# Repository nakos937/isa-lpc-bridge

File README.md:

# isa-lpc-bridge: a real 16-bit ISA slot on a modern motherboard, through the TPM header

A riser board with one **16-bit ISA slot** that connects to a modern PC through its **TPM header (LPC bus)**.
It is meant for **legacy ISA cards under DOS and DOS-based systems**: sound cards (Sound Blaster, Gravis UltraSound, Orpheus II, ...), I/O and
serial cards, and other I/O-mapped cards with IRQ and DMA.
Like [dISAppointment](https://github.com/rasteri/dISAppointment), but with a microcontroller (RP2354B, firmware in C) in
place of the Fintek F85226 bridge chip, so the whole thing is open and tweakable, and does not rely on a custom, hard to get ASIC.

> **Status.** Revision `PASS_HG25` works. Tested by the author with a **Sound Blaster 16, Gravis UltraSound, GUS PnP,
> Orpheus II and a generic OPL3-SAx card** (all working without problems, **including DMA** through the LDRQ# wire) and an ISA **floppy/COM port card**. Cards in the table below that are not marked
> *tested* are expected to work from datasheets and Linux driver sources. Reports and fixes are welcome.

*3D renders from KiCad. The ISA socket and the power connector have no 3D model in the render and show as pads/outline.*

## Base specs

| | |
|---|---|
| Board | 240.1 x 36.1 mm, 4 layers, 1.6 mm, single sided assembly |
| Slot | one 98-pin 16-bit ISA edge socket (ED98KBGFBK, LCSC C5173323) |
| Host link | 2x9 right-angle header wired 1:1 to the common 17/18-pin "TPM header": LCLK, LFRAME#, LAD0-3, SERIRQ, PCIRST#, GND (**3.3 V logic**) |
| LDRQ# | one extra wire, **not on the TPM header** (see [Getting LDRQ#](#getting-ldrq-needed-for-dma)) |
| Power | from the PSU through a 4-pin floppy (Berg) power connector: +5 V and +12 V. -12 V, -5 V and 3.3 V are made on the board |
| MCU | RP2354B (QFN-80, 2 MB internal flash), 400 MHz default, programmed over SWD (no USB on the board) |
| Provides | ISA I/O cycles, 8-bit and 16-bit DMA (channels 0-3 and 5-7), IRQ 3-7, 9-12, 14, 15 and IOCHCK# through SERIRQ, ISA reset |
| Does not provide | ISA memory cycles, bus mastering, refresh, MEMCS16#/OWS# sensing |
| Host tool | `ISALPC.EXE` (DOS) / `isalpc` (Linux): programs the chipset's LPC decode windows and the bridge, with presets for common cards |

```mermaid
flowchart LR
  PCH["PC chipset (PCH)\nLPC bus"] -- "TPM header: LCLK LFRAME# LAD0-3\nSERIRQ PCIRST# GND" --> J4["J4 on the board"]
  PCH -. "LDRQ# (wire from a test point)" .-> J4
  J4 --> MCU["RP2354B\n3 PIO state machines\n= LPC target"]
  MCU --> ISA["address shift registers\nIRQ input registers\n5 V buffers + level shifters"]
  ISA --> SLOT["16-bit ISA slot\n(sound card)"]
  PSU["PSU floppy connector\n+5 V / +12 V"] --> PWR["fuses, filters,\n3.3 V, -12 V, -5 V"] --> SLOT
```

## Contents
1. [Who this is for and what you need](#who-this-is-for-and-what-you-need)
2. [Compatibility](#compatibility)
3. [Mounting it in a case](#mounting-it-in-a-case)
4. [Wiring](#wiring)
5. [Getting LDRQ#](#getting-ldrq-needed-for-dma)
6. [First power-up checklist](#first-power-up-checklist)
7. [Firmware](#firmware)
8. [Host setup: ISALPC](#host-setup-isalpc)
9. [Motherboard BIOS notes](#motherboard-bios-notes)
10. [Building everything](#building-everything)
11. [Repository layout](#repository-layout)
12. [Quirks and limits](#quirks-and-limits)
13. [Credits and licenses](#credits-and-licenses)

## Who this is for and what you need
- A motherboard with a **TPM header that carries the LPC bus** and a chipset whose LPC bridge can forward I/O ranges (Intel PCH
  generic decode ranges; AMD works with [lpcexp](https://github.com/lss4/lpcexp) but is not covered by our tool).
- Soldering skills: the board is assembled by the fab, but you must **wire LDRQ#** to the motherboard (a fine wire to a test
  point or resistor pad) if you want DMA.
- An SWD probe (CMSIS-DAP: Raspberry Pi Debug Probe, a Pico running picoprobe, ...) and OpenOCD to load the firmware.
- A PSU with a spare floppy power plug (the one with 4 wires: red +5 V, black, black, yellow +12 V).
- A DOS boot environment on the host (MS-DOS/FreeDOS/Win9x on a legacy/CSM boot).
- A scope or logic analyser is strongly recommended for bring-up. Nothing has been measured on silicon yet.

## Compatibility

### Motherboards / chipsets
| Host | I/O + IRQ | DMA | Notes |
|---|---|---|---|
| **ASRock Fatal1ty X99M Killer** (Intel X99 / C610) | works | **works** (with the LDRQ# wire) | BIOS analysed in [docs/bios-x99m-killer-p4.01.md](docs/bios-x99m-killer-p4.01.md); 17-pin TPMS1 header |
| Other Intel chipsets **before the 100 series** (6/7/8/9 series, X79/X99/C600) | expected | expected, needs LDRQ# wire | LPC DMA exists on these. Header pinouts differ per board: check with a meter |
| Intel **100 series and newer** (Skylake and later) | expected (GEN decode ranges exist) | **no**: Intel removed LDRQ# from the 100 series on | FM synthesis, MIDI and PIO sound work; digitised audio in DOS games needs DMA and will not. See the [lpcexp readme](https://github.com/lss4/lpcexp) |
| AMD (AM4 and similar) | use lpcexp (AMD code), not `isalpc` | AM4: unknown to us; **AM5/SP5: no LDRQ#** | not covered |

### Sound cards (*tested* = tried by the author; otherwise expected from datasheets and Linux driver sources)
The `ISALPC` presets in parentheses set up the chipset and the bridge for the card.

| Card | Status | Notes |
|---|---|---|
| Sound Blaster 1.x/2.0/Pro, **Sound Blaster 16** (`sb`, `sb16`) | **tested**, works (SB16) | byte I/O only. 8-bit DMA 1, 16-bit DMA 5. IRQ 5/7. MPU-401 at 330 |
| AdLib, OPL2/OPL3 (`adlib`) | expected (the OPL3 on the tested cards works) | ports 388-38B, no IRQ or DMA |
| **Gravis UltraSound** classic (`gus`, `gusmax`) | **tested**, works | base 240; word access on base+0x104 is handled |
| **GUS PnP / AMD InterWave** (`guspnp`) | **tested**, works | needs the ISA PnP ports (279, A79, read port) forwarded: `@pnp` is included |
| **Orpheus II** (`orpheus2`) | **tested**, works | CS4237B + InterWave + OPL3 + PCMIDI; needs all four LPC windows. WSS at 534 collides with the chipset GPIO block on some boards (the X99M): `ISALPC` moves that block, **DOS only** (works on the X99M: tested with the Orpheus II) |
| **AWE32/AWE64** (`awe32`) | expected | the EMU8000 uses 16-bit I/O (ports 620/A20/E20): supported. Needs five 256-port blocks, which is more than the chipset has windows for unless you free the Super I/O and COM decodes |
| **Yamaha OPL3-SAx** (`opl3sa`) | **tested**, works (generic card) | |
| ESS AudioDrive, Crystal CS423x, WSS (`ess`, `cs423x`, `wss`) | expected | WSS base 530 is inside the GPIO block on X99M-like boards (see above) |
| MPU-401 interfaces, Roland SCC-1/LAPC-I (`mpu401`) | expected | the board makes -12 V and -5 V |
| Pro Audio Spectrum 16 | **impossible** | its registers span 19 port blocks, the chipset has four decode windows |
| Turtle Beach MultiSound / Pinnacle / Fiji, any card with an on-board memory window | **not supported** | needs ISA *memory* cycles. UEFI hosts occupy that memory space anyway |
| ADI/Echo PSS | possible | 16-bit reads need an entry in `word_rd` (a commented line is in `fw/src/main.c`) |
| Floppy, COM, LPT, IDE, NE2000, SCSI ISA cards (`fdc`, `com1`, `lpt1`, `ide1`, `ne2000`, ...) | floppy + COM card **tested**, works; the other presets exist but are not the project's goal | disable the onboard ports in the BIOS first, or both answer |

Cards the author has no access to are marked *expected* and have not been tried: more test reports are welcome.

Not intended: ISA VGA cards, bus-mastering cards, cards that need ISA memory.

## Mounting it in a case
- The board is **240 mm long and 36 mm wide**. It is made for a case with **two free PCI/expansion slot positions** next to
  each other (a microATX or ATX board with the lower slots empty); measure your case before ordering.
- There are **no mounting holes**. Hold it with **thick double-sided foam tape or plastic spacers/standoffs under the board**.
  Without support the board flexes when you insert a card: the socket datasheet gives up to 0.4 kgf per contact pair, which is up to roughly 20 kgf for a full 98-pin card, so use a
  firm, even base and push the card in while holding the board down.
- The ISA socket is a straight edge socket: the **card stands up from the board** (its bottom edge sits about 8 mm above
  the PCB). Check clearance to the neighbouring PCIe cards, the case ribs and the card's own bracket. The card bracket
  **may not line up with a case slot** (it depends on your case): expect to leave it unscrewed or use a bracket-less mount.
- Cables leave from the long edge at the right end: the power plug (J1), the SWD header (J2) and the 2x9 TPM-style header
  (J4) are right-angle parts. The tall parts are the three headers and the power connector.
- Keep the LPC wiring **short** (10 cm or less) and use the ground pins of J4.

## Wiring

### Power connector J1 (4-pin floppy/Berg, right angle)
| Pin | Signal |
|---|---|
| 1 | +5 V (red wire) |
| 2, 3 | GND |
| 4 | +12 V (yellow wire) |

Fuses: 2.6 A hold on +5 V, 1.5 A hold on +12 V (resettable). Surge clamps on both rails.

### Host header J4 (2x9, 2.54 mm, right angle)
Wired 1:1 to the ASRock-style TPM header. Pin numbers as on the standard 20-1-pin TPM layout (odd pins in one row, even in
the other; **pin 13 is the key position and missing on the motherboard header**). Always verify against *your* board.

| J4 pin | Signal | Pin | Signal |
|---|---|---|---|
| 1 | LCLK (PCICLK) | 2 | GND |
| 3 | LFRAME# | 4 | not connected |
| 5 | PCIRST# | 6 | not connected |
| 7 | LAD3 | 8 | LAD2 |
| 9 | not connected (+3V on the host) | 10 | LAD1 |
| 11 | LAD0 | 12 | GND |
| **13** | **LDRQ# (100 ohm in series, 4.7 k pull-up to 3.3 V on the board)** | 14 | not connected |
| 15 | not connected (+3VSB on the host) | 16 | SERIRQ |
| 17 | GND | 18 | GND |

The host's +3V, +3VSB, SMBus and S_PWRDWN# pins are **not** connected on purpose.

### SWD header J2 (1x4)
`SWCLK, GND, SWDIO, RUN` (pin 1 at the SWCLK end, marked on the silkscreen).

### Test points
`TP1` +5V_SLOT, `TP2` +12V_SLOT, `TP3` +3V3, `TP4` -12V, `TP5` -5V, `TP6` GND, `TP7` ISA_RUN, `TP8` LCLK, `TP9` BCLK (divided oscillator).

## Getting LDRQ# (needed for DMA)
DMA on the LPC bus is requested by a separate signal, **LDRQ#**. The TPM header does not carry it. You have to take it
from the motherboard yourself. Without it everything else works (I/O cycles, IRQs, FM/OPL music), but anything that needs
DMA (digitised sound in DOS games, SB/GUS sample playback) will not.

1. **Find the signal.** Use the board's boardview. The chipset has an LDRQ0# pin (and some also LDRQ1#). On most boards it runs to the Super I/O chip
   (the one that does COM/LPT/PS-2) and often to a test pad, a series resistor, a 0 ohm link or a via on the way. Look at
   the board's schematic or boardview if you have one, or probe the Super I/O's LDRQ# pin. The signal idles **high at
   3.3 V** and pulses low during a DMA request. It must never be tied to 5 V.
2. **Solder a thin wire** (30 AWG wire-wrap wire is fine) to that point.
3. **Connect the other end to the adapter in one of two ways:**
   - **Directly:** a Dupont jumper wire, or the wire itself, to **J4 pin 13** (the pin that is missing on the motherboard's
     TPM header, so the TPM-style cable can not carry it).
   - **Through the TPM header cable:** if you make or modify a ribbon between the motherboard's TPM header and J4, add the
     wire to the position of pin 13 on the J4 end. Keep the stub short.
4. Keep the wire short, run it next to a ground wire (J4 pins 12/17/18) and away from the clock.
5. **Disable the Super I/O's own LPC DMA users** (floppy, parallel port in ECP mode) in the BIOS, so the Super I/O does not
   drive the same LDRQ# line at the same time.
6. Some chipsets multiplex LDRQ1# with a GPIO. If you picked that pin, `ISALPC ldrq1` switches the pad to LDRQ1#. On the
   author's ASRock X99M Killer (BIOS P4.01) the LDRQ1# pad is already set to its LDRQ function (found by static analysis of the BIOS image).

> **The test point is board specific.** Open your board's **boardview** (or schematic) and look up the LDRQ# / LDRQ0# net
> between the chipset and the Super I/O or the LPC pads. The author's X99M Killer works this way: with the wire in place,
> DMA (digitised audio on the SB16, GUS and Orpheus II) works.

## First power-up checklist
1. Before inserting anything, check **J1 polarity** with a meter: red wire to TP1 (+5 V), yellow to TP2 (+12 V).
2. **Never run the PC with J4 connected and J1 unplugged.** The LPC pins of the MCU are not 5 V tolerant and the host's 3.3 V
   would back-feed an unpowered chip.
3. Plug the PSU connector with the PSU off. Power up *without* the ISA card and *without* J4. Check the rails on the test
   points: +5 V, +12 V, **+3.3 V**, **-12 V (about -12.1 V)** and **-5 V**.
4. Load the firmware over SWD (see below) and check `RESETDRV`/`ISA_RUN` behaviour with a scope.
5. Scope **LCLK** at the MCU pin before connecting J4; the LPC pins are driven by the PIO state machines directly.
6. Connect J4 with the PC off, then power both. Run `ISALPC` and read the status.
7. Only then add a card. Scope the DRQ and IOCHRDY lines at the MCU: if they exceed about 5.4 V with a real card, add a
   series resistor or clamp.
8. Support the board before inserting the card (see [Mounting](#mounting-it-in-a-case)).

## Firmware
Source in [`fw/`](fw/) (pico-sdk 2.1 or newer, `arm-none-eabi-gcc`, cmake, ninja). Pre-built images of build 22:
[`fw/prebuilt/`](fw/prebuilt/) (`isa_lpc_flash_build22.elf`, `isa_lpc_ram_build22.elf`).

- **Architecture:** three PIO blocks implement the LPC target (front end, reply script player, LDRQ#/SERIRQ engines);
  core 1 claims LPC cycles within the 3-clock SYNC deadline; core 0 runs the ISA bus (address through the shift
  registers, strobes, IOCHRDY waits, DMA). Details in [fw/README.md](fw/README.md) and [docs/firmware-review.md](docs/firmware-review.md).
- **Flash:** `fw/tools/flash.sh` (OpenOCD + CMSIS-DAP probe on J2). There is **no USB/BOOTSEL** on the board.
- **No flash needed for development:** `fw/tools/ram.sh` loads the RAM image over SWD; tuning values live in a RAM block
  at `0x2007C000` and can be changed live with OpenOCD (`fw/tools/isa.tcl`).
- **Config port:** the bridge answers on I/O ports **4E/4F** (like the Fintek chip); `ISALPC` uses it. Index 'I','S','A' unlocks
  it. It can be turned off with a flag.
- **Saved config:** `ISALPC ... SAVE` keeps the bridge settings (port filter, IRQ list, timing) in the MCU flash, so the bridge
  answers correctly right after power-up. `ISALPC FORGET` erases them. A save pauses the bridge for up to 1.3 s. Settings
  that could lock the host out are never restored from flash.
- **Tests without hardware:** `python3 fw/sim/test_lpc.py`, `python3 fw/sim/test_aux.py` (cycle simulator of the PIO programs),
  `cc -Ifw/src -o /tmp/t fw/test/io16_test.c && /tmp/t`, same for `cfgport_test.c`.

## Host setup: ISALPC
The chipset forwards only the I/O ranges it was told to, and the bridge claims only the ports of the card you use.
`ISALPC` (DOS, `host/ISALPC.EXE`) or `isalpc` (Linux, as root) does both. **Run it after every boot** (the chipset
windows are reset by the BIOS; the bridge settings live in RAM unless you `SAVE` them): put it in `AUTOEXEC.BAT` before the sound drivers.

```
ISALPC                      show decode windows, SERIRQ, PCI IRQs and the bridge state (writes nothing)
ISALPC SB16                 Sound Blaster 16 at 220, MPU at 330, OPL at 388, game port
ISALPC SB16 FORCE DRY       print what it would do, change nothing
ISALPC GUS=240              Gravis UltraSound at base 240
ISALPC ORPHEUS2 FORCE       Orpheus II: replaces BIOS windows as needed
ISALPC AWE32 FORCE NOPIRQ   AWE32, also turns PCI interrupt routing off for the IRQs the bridge serves
ISALPC LIST                 all presets
```
Options: `SAVE` stores the bridge settings in its flash (`FORGET` erases them), `FORCE` replaces decode windows the BIOS set (as few as needed, highest window first, and it says which),
`DRY` changes nothing, `DMA` resets the DMA controllers (default on DOS), `LDRQ1` switches the GPIO pad to LDRQ1#,
`NOPIRQ` stops routing PCI interrupts to the IRQs the bridge serves, `IRQ=5,7` sets the served IRQs exactly, `GPIO=680` chooses where the chipset GPIO block moves
when a card needs ports inside it (**DOS only**: ACPI operating systems expect the old address).

Limits you will hit: four decode windows of up to 256 ports each, one 256-port block per window; port 279 (ISA PnP address)
is read-only through the LPT decode, so PnP cards need a window. The tool refuses ports inside the chipset's own register
blocks. The DOS part needs Open Watcom to build.

Linux: `cc -O2 -o isalpc host/isalpc.c`, run as root. DOS: `make -C host ISALPC.EXE` with Open Watcom, or use the prebuilt EXE.

## Motherboard BIOS notes
- **Disable onboard COM, LPT, floppy and anything else on the LPC bus you do not need.** They compete for the same ports
  and DMA channels and some use LPC windows the card needs. Keep CSM/legacy boot and legacy USB (for a DOS keyboard).
- No setup option reserves an IRQ for ISA cards: a PCI device can land on the card's IRQ. `ISALPC` lists the IRQs PCI uses
  and `NOPIRQ` can take them away from PCI.
- Serial IRQ must be in **continuous** mode. `ISALPC` sets it; the bridge does not work in quiet mode.
- **ASRock X99M Killer 3.1 BIOS P4.01**: analysed in [docs/bios-x99m-killer-p4.01.md](docs/bios-x99m-killer-p4.01.md): three of the four
  generic decode windows are used, the chipset GPIO block sits at 500-57F (collides with WSS/Orpheus at 530/534), serial IRQ
  starts in quiet mode. An optional patcher ([tools/bios/patch_x99m.py](tools/bios/patch_x99m.py)) frees the unused windows
  from power-on (7 bytes). It checks the sha256 of the original image and edits only what it recognises. Flash modified firmware only if you have an SPI programmer
  and a backup. `ISALPC` does the same at run time, so the patch is optional.

## Building everything
| What | How |
|---|---|
| Firmware | `export PICO_SDK_PATH=...; fw/tools/build.sh` (flash image) or `fw/tools/build.sh ram` |
| DOS tool | Open Watcom 2: `make -C host ISALPC.EXE` (16-bit small model) |
| Linux tool | `cc -O2 -o isalpc host/isalpc.c` |
| Tool self-test | `make -C host test` (fake chipset + the firmware's config-port code) |
| Netlist | `python3 sch/build.py` (SKiDL, KiCad 10 libraries), `python3 tools/netcheck.py` |
| Board | open `pcb/PASS_HG25.kicad_pcb` in **KiCad 10**; custom footprints in `lib/isa_bridge.pretty` (add to your footprint table) |
| Fab files | `fab/PASS_HG25_gerbers.zip`, `fab/bom.csv`, `fab/cpl.csv` (JLCPCB format, LCSC numbers in the BOM) |
| Datasheets | `docs/datasheets/` (index in its README) |
| Independent clearance audit | `tools/review/via_copper_audit.py` (KiCad Python) |

## Repository layout
```
pcb/       KiCad 10 board (PASS_HG25), project and design rules (JLCPCB multilayer minimums)
fab/       gerbers, BOM, placement file, LCSC part map
sch/       build.py: the whole netlist as SKiDL code (no .kicad_sch files)
lib/       custom footprints and symbols, datasheet pin tables
fw/        RP2354B firmware, PIO programs, simulator, tests, prebuilt images
host/      ISALPC (DOS and Linux) and its self-test
tools/     netlist checker, symbol generator, BIOS analysis scripts, clearance audit
docs/      pin map, BIOS analysis, card I/O survey, reviews, order notes
images/    renders
```

## Quirks and limits
- Run `ISALPC` at every boot: the BIOS resets the chipset's decode windows each time. The bridge's own settings can be kept in its flash with `ISALPC ... SAVE`, otherwise they are lost at power-off.
- 5 V logic on the ISA side through buffers; the MCU side is 3.3 V. `IOCS16#` is sensed after each address change.
- There is no USB, no BOOTSEL button: a failed flash needs an SWD probe. The RAM image avoids flashing altogether.
- The hand-wired LDRQ# makes this a **hobby/experimenter board**, not a plug-and-play product.
- 400 MHz at 1.30 V is the default (allowed window 340-500 MHz). Put a heatsink the size of the MCU (10 x 10 mm) on it with thermal tape.
- ISA PnP cards need a decode window for the PnP ports; combined with a four-window limit this restricts what fits
  (AWE32 + PnP does not).

## Credits and licenses
- Idea and the DOS tool's concept: **rasteri's [dISAppointment](https://github.com/rasteri/dISAppointment)** (CC BY-SA 4.0): ISA socket
  footprint, pull-up network, `sapphisa`; **[lpcexp](https://github.com/lss4/lpcexp)** (CC BY-SA 4.0): chipset
  register programming; both share the DMA reset register list with `ISALPC`. The MCU power circuit follows Raspberry Pi's RP2350 minimal design (MIT).
- **Board, firmware, host tool, scripts, docs: GPL-2.0-or-later.** The ISA socket footprint and the pull-up
  values come from dISAppointment and stay CC BY-SA 4.0.
  See [LICENSE.md](LICENSE.md) and [LICENSES/](LICENSES/).
- No warranty. Plugging a PSU into a board you assembled yourself, and wiring to a motherboard with a soldering iron,
  can destroy both. You do it at your own risk.

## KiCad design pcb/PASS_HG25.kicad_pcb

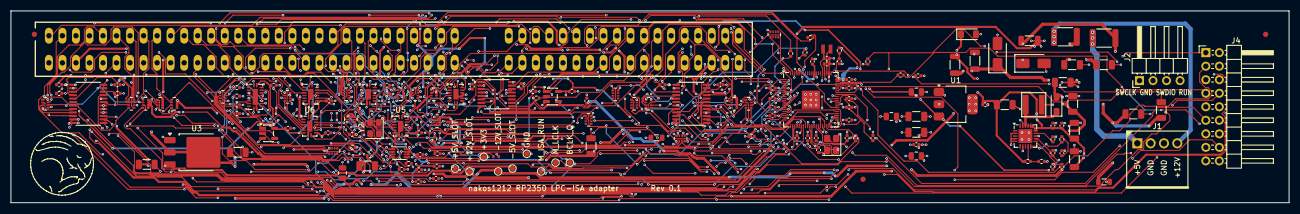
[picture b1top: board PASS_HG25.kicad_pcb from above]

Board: 4 copper layers, 240.0 x 36.0 mm, 166 parts (0 on the bottom side), 189 nets.

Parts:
C1: 47u/10V; C_1206_3216Metric
C2, C4, C21, C22, C26, C28, C67: 10u/25V; C_1206_3216Metric
C3, C7, C14: 22u/25V; C_1206_3216Metric
C5, C16, C17: 22u/10V; C_1206_3216Metric
C6, C8, C10, C11, C12, C13, C15, C23, C33, C34, C35, C36, C37, C38, C39, C40, C41, C42, C43, C44, C45, C50, C51, C52, C53, C54, C55, C56, C57, C58, C59, C60, C61, C62, C63, C64, C65, C66, C68, C69: 100n; C_0402_1005Metric
C9, C18, C46, C47: 10u/10V; C_0805_2012Metric
C19, C20: 1u/16V; C_0402_1005Metric
C24: 1u/25V; C_0402_1005Metric
C25: 10u/50V; C_1206_3216Metric
C27: 22n; C_0402_1005Metric
C29, C30, C31, C32: 4.7u/10V; C_0402_1005Metric
C48, C49: 15p; C_0402_1005Metric
D1: SMAJ5.0A; D_SMA
D2: SMAJ13A; D_SMA
D3: SMF12A; D_SOD-123FL_1.1x1.5
D4: DFLS240; D_SOD-123FL_1.1x1.5
F1: 1812L260/12MR; Fuse_1812_4532Metric
F2: 1812L150/24MR; Fuse_1812_4532Metric
FB1, FB2, FB4: BLM31KN601SN1L; L_1206_3216Metric
FB3, FB5: BLM21PG221SN1D; L_0805_2012Metric
FID1, FID2, FID3: Fiducial
G1: rabbit
J1: Berg_Floppy_Power_4P; Berg_171826-4_1x04_P2.50mm
J2: PROG_SWD; PinHeader_1x04_P2.54mm_Horizontal
J3: ISA_16bit_Socket; ISA
J4: TPMS1_LPC; PinHeader_2x09_P2.54mm_Horizontal
L1: 15u NR4030S150MT; L_NR4030
L2: 3.3u AOTA-B201610S3R3-101-T; L_Abracon_AOTA-B201610S3R3-101-T
R1: 200k; R_0402_1005Metric
R2: 47k; R_0402_1005Metric
R3: 1M; R_0402_1005Metric
R4: 62k; R_0402_1005Metric
R5: 15k; R_0402_1005Metric
R6, R21, R22, R23, R24, R25, R26: 33; R_0402_1005Metric
R7, R18: 1k; R_0402_1005Metric
R8, R14, R15, R16, R17, R27: 10k; R_0402_1005Metric
R9, R10, R11, R12, R13, R19: 4.7k; R_0402_1005Metric
R20: 100; R_0402_1005Metric
RN1, RN2: 1k; R_Array_Convex_4x0402
RN3, RN4, RN5, RN16, RN17: 4.7k; R_Array_Convex_4x0402
RN6, RN7, RN8, RN9, RN10, RN11, RN12, RN13, RN14, RN15: 8.2k; R_Array_Convex_4x0402
RN18: 33; R_Array_Convex_4x0402
RN19, RN20, RN21, RN22: 68; R_Array_Convex_4x0402
TP1: +5V_SLOT; TestPoint_Pad_D1.0mm
TP2: +12V_SLOT; TestPoint_Pad_D1.0mm
TP3: +3V3; TestPoint_Pad_D1.0mm
TP4: -12V_SLOT; TestPoint_Pad_D1.0mm
TP5: -5V_SLOT; TestPoint_Pad_D1.0mm
TP6: GND; TestPoint_Pad_D1.0mm
TP7: M_ISA_RUN; TestPoint_Pad_D1.0mm
TP8: M_LCLK; TestPoint_Pad_D1.0mm
TP9: BCLK_Q; TestPoint_Pad_D1.0mm
U1: BL9110-330BPFB; SOT-223-3_TabPin2
U2: ADP5071ACPZ; LFCSP-20-1EP_4x4mm_P0.5mm_EP2.6x2.6mm
U3: MC79M05CDTG; TO-252-3_TabPin2
U4: RP2354B; QFN-80-1EP_10x10mm_P0.4mm_EP3.4x3.4mm
U5, U6, U7: SN74AHCT595; DHVQFN-16-1EP_2.5x3.5mm_P0.5mm_EP1x2mm
U8, U9: SN74LVC165A; DHVQFN-16-1EP_2.5x3.5mm_P0.5mm_EP1x2mm
U10: SN74AHCT244; DHVQFN-20-1EP_2.5x4.5mm_P0.5mm_EP1x3mm
U11: 74AHCT138; TSSOP-16_4.4x5mm_P0.65mm
U12, U13: SN74LVC4245A; TSSOP-24_4.4x7.8mm_P0.65mm
U14: 74LVC2G74; VSSOP-8_2.3x2mm_P0.5mm
U15: 74AHCT1G125; SOT-23-5
U16: 74AHCT1G00; SOT-23-5
Y1: 12MHz ABM8-272-T3; Crystal_SMD_3225-4Pin_3.2x2.5mm
Y2: ASE-14.31818MHZ-L-C-T; Oscillator_SMD_Abracon_ASE-4Pin_3.2x2.5mm

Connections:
+1V1: C30.1, C31.1, C33.1, C34.1, C35.1, C68.1, L2.1, U4.10, U4.32, U4.51, U4.65
+3V3: C16.1, C17.1, C29.1, C36.1, C37.1, C38.1, C39.1, C40.1, C41.1, C42.1, C43.1, C44.1, C45.1, C46.1, C47.1, C54.1, C55.1, C59.1, C61.1, FB5.1, R6.1, R8.1, R9.2, R10.2, R11.2, R12.2, R13.2, R27.2, RN3.8, TP3.1, U1.2, U4.5, U4.15, U4.24, U4.29, U4.41, U4.50, U4.59, U4.60, U4.64, U4.68, U4.69, U4.76, U8.16, U9.16, U12.23, U12.24, U13.23, U13.24
+3V3_OSC: C18.1, C62.1, C63.1, C64.1, C69.1, FB5.2, U14.6, U14.7, U14.8, Y2.1, Y2.4
+5V_IN: C1.1, C2.1, D1.1, F1.2, FB1.1, FB3.1
+5V_LOG: C9.1, C10.1, C11.1, C12.1, C13.1, C51.1, C52.1, C53.1, C56.1, C57.1, C58.1, C60.1, C65.1, C66.1, FB3.2, U1.3, U5.10, U5.16, U6.10, U6.16, U7.10, U7.16, U10.20, U11.16, U12.1, U13.1, U15.5, U16.5
+5V_SLOT: C5.1, C6.1, FB1.2, J3.3, J3.29, J3.78, R18.2, R19.2, RN1.5, RN1.6, RN1.7, RN1.8, RN2.8, RN4.6, RN4.7, RN4.8, RN6.7, RN6.8, RN9.5, RN9.6, RN9.7, RN10.5, RN10.6, RN10.7, RN10.8, RN11.5, RN11.6, RN11.7, RN11.8, RN12.5, RN12.6, RN12.7, RN12.8, RN13.5, RN13.6, RN13.7, RN13.8, RN14.5, RN14.6, RN14.7, RN14.8, RN15.8, TP1.1
+12V_IN: C3.1, C4.1, D2.1, F2.2, FB2.1, FB4.1
+12V_PUMP: C14.1, C15.1, C21.1, C22.1, C23.1, C24.1, D3.1, FB4.2, R1.1, U2.15, U2.16, U2.17
+12V_SLOT: C7.1, C8.1, FB2.2, J3.9, TP2.1
-5V_SLOT: C28.1, J3.5, TP5.1, U3.3
-12V_SLOT: C25.1, C26.1, C67.1, D4.2, J3.7, R3.1, TP4.1, U3.2
AEN: J3.42, U10.14
BALE: J3.28, R18.1
BCLK: J3.20, RN18.6
BCLK_Q: R21.2, TP9.1, U15.2
BCLK_Q_RAW: R21.1, U14.5
BCLK_o: RN18.3, U15.4
CHAIN_C1: U5.9, U6.14
CHAIN_C2: U6.9, U7.14
COMP2_N: C27.1, R5.2
DACK0#: J3.70, U11.15
DACK1#: J3.17, U11.14
DACK2#: J3.26, U11.13
DACK3#: J3.15, U11.12
DACK5#: J3.72, U11.10
DACK6#: J3.74, U11.9
DACK7#: J3.76, U11.7
DRQ0: J3.71, RN16.1, U4.40
DRQ1: J3.18, RN5.1, U4.42
DRQ2: J3.6, RN16.2, U4.43
DRQ3: J3.16, RN5.2, U4.44
DRQ5: J3.73, RN16.3, U4.45
DRQ6: J3.75, RN16.4, U4.46
DRQ7: J3.77, RN17.1, U4.47
EN2_DIV: R1.2, R2.1, U2.9
GND: C1.2, C2.2, C3.2, C4.2, C5.2, C6.2, C7.2, C8.2, C9.2, C10.2, C11.2, C12.2, C13.2, C14.2, C15.2, C16.2, C17.2, C18.2, C19.2, C20.2, C21.2, C22.2, C23.2, C24.2, C25.2, C26.2, C27.2, C28.2, C29.2, C30.2, C31.2, C32.2, C33.2, C34.2, C35.2, C36.2, C37.2, C38.2, C39.2, C40.2, C41.2, C42.2, C43.2, C44.2, C45.2, C46.2, C47.2, C48.2, C49.2, C50.2, C51.2, C52.2, C53.2, C54.2, C55.2, C56.2, C57.2, C58.2, C59.2, C60.2, C61.2, C62.2, C63.2, C64.2, C65.2, C66.2, C67.2, C68.2, C69.2, D1.2, D2.2, D3.2, J1.2, J1.3, J2.2, J3.1, J3.10, J3.31, J3.80, J4.2, J4.12, J4.17, J4.18, L1.2, R2.2, R14.2, R15.2, R16.2, R17.2, RN5.7, RN5.8, RN6.5, RN6.6, RN7.5, RN7.6, RN7.7, RN7.8, RN8.5, RN8.6, RN8.7, RN8.8, RN9.8, RN16.5, RN16.6, RN16.7, RN16.8, RN17.8, TP6.1, U1.1, U2.2, U2.4, U2.5, U2.7, U2.13, U2.19, U2.21, U3.1, U4.62, U4.81, U5.8, U5.17, U6.8, U6.17, U7.8, U7.17, U8.8, U8.15, U8.17, U9.8, U9.10, U9.11, U9.12, U9.13, U9.15, U9.17, U10.1, U10.10, U10.11, U10.13, U10.15, U10.17, U10.19, U10.21, U11.4, U11.5, U11.8, U12.11, U12.12, U12.13, U13.11, U13.12, U13.13, U14.4, U15.1, U15.3, U16.3, Y1.2, Y1.4, Y2.2
IOCHCK#: J3.32, RN4.1, U9.3
IOCHRDY: J3.41, RN3.1, U4.11
IOCS16#: J3.64, RN1.1, U8.6
IOR#: J3.14, RN6.1, RN18.8
IOR#_o: RN18.1, U10.18
IOW#: J3.13, RN6.2, RN18.7
IOW#_o: RN18.2, U10.16
IRQ3: J3.25, RN7.4, U9.14
IRQ4: J3.24, RN8.1, U8.5
IRQ5: J3.23, RN8.2, U8.4
IRQ6: J3.22, RN8.3, U8.3
IRQ7: J3.21, RN8.4, U8.14
IRQ9: J3.4, RN9.1, U8.13
IRQ10: J3.65, RN6.3, U8.12
IRQ11: J3.66, RN6.4, U8.11
IRQ12: J3.67, RN7.1, U9.6
IRQ14: J3.69, RN7.2, U9.5
IRQ15: J3.68, RN7.3, U9.4
LA17: J3.88, RN9.2
LA18: J3.87, RN9.3
LA19: J3.86, RN9.4
LA20: J3.85, RN10.1
LA21: J3.84, RN10.2
LA22: J3.83, RN10.3
LA23: J3.82, RN10.4
MASTER#: J3.79, RN11.1
MEMCS16#: J3.63, RN1.2
MEMR#: J3.89, RN4.2
MEMW#: J3.90, RN4.3
M_AEN: R15.1, U4.80, U10.6, U11.6
M_CHAIN_MISO: U4.1, U8.9
M_CHAIN_MOSI: U4.4, U5.14
M_CHAIN_RCLK: U4.2, U5.12, U6.12, U7.12
M_CHAIN_SCK: R22.2, U5.11, U6.11, U7.11, U8.2, U9.2
M_CHAIN_SCK_o: R22.1, U4.3
M_CHAIN_SHLD: R12.1, U4.6, U8.1, U9.1
M_DACK_A: U4.77, U11.1
M_DACK_B: U4.78, U11.2
M_DACK_C: U4.79, U11.3
M_IOR_N: R23.2, U10.2
M_IOR_N_o: R9.1, R23.1, U4.7
M_IOW_N: R24.2, U10.4
M_IOW_N_o: R10.1, R24.1, U4.8
M_ISA_RUN: R14.1, TP7.1, U4.13, U16.1
M_LAD0: J4.11, U4.49
M_LAD1: J4.10, U4.52
M_LAD2: J4.8, U4.53
M_LAD3: J4.7, U4.54
M_LCLK: J4.1, R25.2, TP8.1
M_LCLK_o: R25.1, U4.56
M_LDRQ_N: R13.1, R20.1, U4.58
M_LFRAME_N: J4.3, U4.55
M_PCIRST_N: J4.5, R27.1, U4.14, U16.2
M_SD0: U4.16, U12.21
M_SD1: U4.17, U12.20
M_SD2: U4.18, U12.19
M_SD3: U4.19, U12.18
M_SD4: U4.20, U12.17
M_SD5: U4.21, U12.16
M_SD6: U4.22, U12.15
M_SD7: U4.23, U12.14
M_SD8: U4.25, U13.21
M_SD9: U4.26, U13.20
M_SD10: U4.27, U13.19
M_SD11: U4.28, U13.18
M_SD12: U4.36, U13.17
M_SD13: U4.37, U13.16
M_SD14: U4.38, U13.15
M_SD15: U4.39, U13.14
M_SD_DIR: R17.1, U4.48, U12.2, U13.2
M_SD_OE_N: R11.1, U4.9, U12.22, U13.22
M_SERIRQ: J4.16, U4.57
M_TC: R16.1, U4.12, U10.8
unnamed: F1.1, J1.1
unnamed: F2.1, J1.4
unnamed: C19.1, U2.14
unnamed: C20.1, R4.2, U2.12
unnamed: R3.2, R4.1, U2.11
unnamed: R5.1, U2.10
unnamed: U8.10, U9.9
unnamed: U14.2, U14.3
unnamed: J4.13, R20.2
OSC_RAW: R26.1, U14.1, Y2.3
OSC_SLOT: J3.30, R26.2
OWS#: J3.8, RN1.3
REFRESH#: J3.19, R19.1
RESETDRV: RN18.4, U5.13, U6.13, U7.13, U16.4
RESETDRV_S: J3.2, RN18.5
RUN: C50.1, J2.4, R8.2, U4.35
SA0: J3.62, U5.15
SA1: J3.61, U5.1
SA2: J3.60, U5.2
SA3: J3.59, U5.3
SA4: J3.58, U5.4
SA5: J3.57, U5.5
SA6: J3.56, U5.6
SA7: J3.55, U5.7
SA8: J3.54, U6.15
SA9: J3.53, U6.1
SA10: J3.52, U6.2
SA11: J3.51, U6.3
SA12: J3.50, U6.4
SA13: J3.49, U6.5
SA14: J3.48, U6.6
SA15: J3.47, U6.7
SA16: J3.46, U7.1
SA17: J3.45, U7.2
SA18: J3.44, U7.3
SA19: J3.43, U7.4
SBHE#: J3.81, U7.15
SD0: J3.40, RN11.2, RN19.8
SD0_o: RN19.1, U12.3
SD1: J3.39, RN11.3, RN19.7
SD1_o: RN19.2, U12.4
SD2: J3.38, RN13.2, RN19.6
SD2_o: RN19.3, U12.5
SD3: J3.37, RN13.3, RN19.5
SD3_o: RN19.4, U12.6
SD4: J3.36, RN13.4, RN20.8
SD4_o: RN20.1, U12.7
SD5: J3.35, RN14.1, RN20.7
SD5_o: RN20.2, U12.8
SD6: J3.34, RN14.2, RN20.6
SD6_o: RN20.3, U12.9
SD7: J3.33, RN14.3, RN20.5
SD7_o: RN20.4, U12.10
SD8: J3.91, RN14.4, RN21.8
SD8_o: RN21.1, U13.3
SD9: J3.92, RN15.1, RN21.7
SD9_o: RN21.2, U13.4
SD10: J3.93, RN11.4, RN21.6
SD10_o: RN21.3, U13.5
SD11: J3.94, RN12.1, RN21.5
SD11_o: RN21.4, U13.6
SD12: J3.95, RN12.2, RN22.8
SD12_o: RN22.1, U13.7
SD13: J3.96, RN12.3, RN22.7
SD13_o: RN22.2, U13.8
SD14: J3.97, RN12.4, RN22.6
SD14_o: RN22.3, U13.9
SD15: J3.98, RN13.1, RN22.5
SD15_o: RN22.4, U13.10
SMEMR#: J3.12, RN1.4
SMEMW#: J3.11, RN2.1
SW2_INV: D4.1, L1.1, U2.18
SWCLK: J2.1, U4.33
SWDIO: J2.3, U4.34
TC: J3.27, U10.12
VREG_AVDD: C32.1, R6.2, U4.61
VREG_LX: L2.2, U4.63
XIN: C48.1, U4.30, Y1.1
XOUT: R7.1, U4.31
XOUT_X: C49.1, R7.2, Y1.3

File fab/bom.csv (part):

Comment,Designator,Footprint,LCSC Part #,MPN,Source note,JLC class,Stock
47u/10V,C1,C_1206_3216Metric,C96123,CL31A476MPHNNNE,"Basic, 47 uF 10 V X5R 1206 ; swapped from 1210 to 1206 (Basic/Preferred library has no 1210 part; avoids the 3.07 USD Extended feeder fee); DC bias not verified (Samsung general catalog has no per-part curve); bulk or output-filter use, no loop depends on it",Basic,449969
10u/25V,"C2,C4,C21,C22,C25,C26,C28,C67",C_1206_3216Metric,C13585,CL31A106KBHNNNE,"Basic, 10 uF 50 V X5R 1206 (50 V part keeps more capacitance at 12 V than the 25 V part); JLC parts library 2026-11-08, swapped to avoid the 3.07 USD Extended feeder fee",Basic,3749704
22u/25V,"C3,C7,C14",C_1206_3216Metric,C12891,CL31A226KAHNNNE,"Basic, 22 uF 25 V X5R 1206 ; swapped from 1210 to 1206 (Basic/Preferred library has no 1210 part; avoids the 3.07 USD Extended feeder fee); DC bias not verified (Samsung general catalog has no per-part curve); bulk or output-filter use, no loop depends on it",Basic,1980959
22u/10V,"C5,C16,C17",C_1206_3216Metric,C5672,CL31A226KPHNNNE,"Preferred part, 1206 22 uF 10 V X5R, 200985 in stock, 0.0738 USD; DC-bias not compared; JLC parts library search 2026-11-08",Preferred,195892
100n,"C6,C8,C10,C11,C12,C13,C15,C23,C33,C34,C35,C36,C37,C38,C39,C40,C41,C42,C43,C44,C45,C50,C51,C52,C53,C54,C55,C56,C57,C58,C59,C60,C61,C62,C63,C64,C65,C66,C68,C69",C_0402_1005Metric,C1525,CL05B104KO5NNNC,"Basic part, 0.0031 USD; JLC parts library search 2026-11-08",Basic,33512849
10u/10V,"C9,C18,C46,C47",C_0805_2012Metric,C15850,CL21A106KAYNNNE,"Basic, 10 uF 25 V X5R 0805 (25 V part keeps more capacitance at 3.3/5 V than the 10 V part); JLC parts library 2026-11-08, swapped to avoid the 3.07 USD Extended feeder fee",Basic,8447152
1u/16V,"C19,C20,C24",C_0402_1005Metric,C52923,CL05A105KA5NQNC,"Basic part, 0.0058 USD, rated 25 V (>= 16 V); JLC parts library search 2026-11-08",Basic,11359732
22n,C27,C_0402_1005Metric,C1532,0402B223K500NT,"Basic; CC2 of the ADP5071 inverter (HG23, was 47 nF Extended)",Basic,554463
4.7u/10V,"C29,C30,C31,C32",C_0402_1005Metric,C23733,CL05A475MP5NRNC,"Basic part, 0.0118 USD; JLC parts library search 2026-11-08",Basic,1004888
15p,"C48,C49",C_0402_1005Metric,C1548,0402CG150J500NT,"Basic part, 15 pF C0G 50 V +-5 %, 0.0026 USD; JLC parts library search 2026-11-08",Basic,1181758
SMAJ5.0A,D1,D_SMA,C2925443,SMAJ5.0A,"Preferred, SMA 400 W 5 V standoff, Vc 9.2 V at 43.5 A; JLC parts library 2026-11-08, swapped to avoid the 3.07 USD Extended feeder fee",Preferred,100734
SMAJ13A,D2,D_SMA,C19077533,SMAJ13A,"Preferred, SMA 400 W 13 V standoff, Vc 21.5 V at 18.6 A; JLC parts library 2026-11-08, swapped to avoid the 3.07 USD Extended feeder fee",Preferred,40366
SMF12A,D3,D_SOD-123FL_1.1x1.5,C19077506,SMF12A,"Preferred, SOD-123FL 200 W 12 V standoff, VBR 14.7 V, Vc 19.9 V at 10.1 A (same figures as the Littelfuse sheet read earlier); JLC parts library 2026-11-08, swapped to avoid the 3.07 USD Extended feeder fee",Preferred,326547
DFLS240,D4,D_SOD-123FL_1.1x1.5,C22466352,DSK24,"Preferred, SOD-123FL Schottky 2 A 40 V, 550 mV at 2 A, 500 uA at 40 V; JLC parts library 2026-11-08, swapped to avoid the 3.07 USD Extended feeder fee",Preferred,2441720
1812L260/12MR,F1,Fuse_1812_4532Metric,C151171,1812L260/12MR,"LCSC page: 2.6 A hold, 5 A trip, 12 V; 815 in stock (snapshot)",Extended,288
1812L150/24MR,F2,Fuse_1812_4532Metric,C142805,1812L150/24MR,"LCSC page lists this MPN: 1.5 A hold, 3 A trip, 24 V; 29k-57k in stock (snapshots)",Extended,11284
BLM31KN601SH1L,"FB1,FB2,FB4",L_1206_3216Metric,C237603,BLM31KN601SH1L,"JLC library 2026-11-11: 215 in stock; same Murata part in the SH grade (600 ohm, 2.9 A, 38 mohm). C668306 (SN1L) had 2 left, 3 needed per board",Extended,215
BLM21PG221SN1D,"FB3,FB5",L_0805_2012Metric,C85840,BLM21PG221SN1D,LCSC listing,Extended,64744
Berg_Floppy_Power_4P,J1,Berg_171826-4_1x04_P2.50mm,C590635,171826-4,"LCSC page: right angle 1x4P 2.5 mm, through hole, 10975 in stock, 0.4868 USD; JLC parts library: Extended, assembly type Wave Soldering",Extended,10970
PROG_SWD,J2,PinHeader_1x04_P2.54mm_Horizontal,C91552,2.54-1*4P reverse bent pin header,"right angle 1x4P 2.54 mm, gold, brass, square pin, mating 6 mm, insulation height 2.54 mm; JLC in-house stock 607 (stock 17693), 0.0143 USD at 1: cheapest candidate with in-house stock in the LCSC list the user pasted (172 codes, none Basic/Preferred; the whole Basic+Preferred library has no connector); swapped 2026-11-09, previous C32713263 (hanxia, 0.0189, in-house 215), originally C42431821",Extended,17687
ISA_16bit_Socket,J3,ISA,C5173323,ED98KBGFBK,"user-chosen cheapest: LCSC 1.2275 USD at 1 (1.021 at 10), 29 in stock; JLC library Extended, assembly type Wave Soldering. Datasheet pattern = our ISA footprint (row 5.08, pitch 2.54, 31 + 10.16 gap + 18, span 129.54, hole 1.0). Contact: brass, 1 microinch gold flash (code BGF). Alternative with 10 microinch gold on phosphor bronze: Sullins EBC49DCWN-S420 C4883475 (6.16 USD, stock 0 pre-sale)",Extended,29
TPMS1_LPC,J4,PinHeader_2x09_P2.54mm_Horizontal,C41417357,HX PZ2.54-2x9P WC-A,"LCSC page: right angle, 2 rows, 18P, 2.54 mm, plastic height 2.5 mm, mating pin 6 mm, tail 3 mm, 885 in stock, 0.1427 USD; JLC parts library / LCSC page 2026-11-08",Extended,886
15u NR4030S150MT,L1,L_NR4030,C28642356,NR4030S150MT,"4x4 mm, land pattern a 1.9 b 1.1 c 3.7 from its datasheet (footprint L_NR4030), 2269 in stock, 0.0385 USD, 15 uH, Isat 1.8 A, Irms 1.2 A, DCR 213 mohm (JLC attributes); JLC parts library 2026-11-08",Extended,2269
3.3u AOTA-B201610S3R3-101-T,L2,L_Abracon_AOTA-B201610S3R3-101-T,C42411119,AOTA-B201610S3R3-101-T,LCSC listing,Extended,1418
200k,R1,R_0402_1005Metric,C25764,0402WGF2003TCE,"Basic, 1 %; JLC parts library search 2026-11-08",Basic,3660772
47k,R2,R_0402_1005Metric,C25792,0402WGF4702TCE,"Basic, 1 %; EN2 divider 200k/47k gives 2.28 V from 12 V (threshold 1.15 V, abs max 6 V); JLC parts library 2026-11-08, swapped to avoid the 3.07 USD Extended feeder fee",Basic,6079366
1M,R3,R_0402_1005Metric,C26083,0402WGF1004TCE,"Basic, 1 %; ADP5071 RFT2 (HG23)",Basic,2700485
62k,R4,R_0402_1005Metric,C37825,0402WGF6202TCE,"Extended, 1 %, 419297 in stock; ADP5071 RFB2: 1M/62k gives -12.10 V (HG23); no Basic/Preferred pair reaches -12 V",Extended,419297
15k,R5,R_0402_1005Metric,C25756,0402WGF1502TCE,"Basic, 1 %; JLC parts library search 2026-11-08",Basic,2337428
33,"R6,R21,R22,R23,R24,R25,R26",R_0402_1005Metric,C25105,0402WGF330JTCE,"Basic, 1 %; JLC parts library search 2026-11-08",Basic,3608292
1k,"R7,R18",R_0402_1005Metric,C11702,0402WGF1001TCE,"Basic, 1 %; JLC parts library search 2026-11-08",Basic,33479298
10k,"R8,R14,R15,R16,R17,R27",R_0402_1005Metric,C25744,0402WGF1002TCE,"Basic, 1 %; JLC parts library search 2026-11-08",Basic,22319276
4.7k,"R9,R10,R11,R12,R13,R19",R_0402_1005Metric,C25900,0402WGF4701TCE,"Basic, 1 %; JLC parts library search 2026-11-08",Basic,15571471
100,R20,R_0402_1005Metric,C25076,0402WGF1000TCE,"Basic, 1 %; JLC parts library search 2026-11-08",Basic,11644706
1k 4x0402,"RN1,RN2",R_Array_Convex_4x0402,C25726,4D02WGJ0102TCE,"Uniroyal 4x0402 array +-5 %, JLC parts library search 2026-11-08 (same family as the 8.2k and 68 ohm arrays)",Extended,97574
4.7k 4x0402,"RN3,RN4,RN5,RN16,RN17",R_Array_Convex_4x0402,C29586,4D02WGJ0472TCE,"Uniroyal 4x0402 array +-5 %, JLC parts library search 2026-11-08 (same family as the 8.2k and 68 ohm arrays)",Extended,155882
8.2k,"RN6,RN7,RN8,RN9,RN10,RN11,RN12,RN13,RN14,RN15",R_Array_Convex_4x0402,C26079,4D02WGJ0822TCE,LCSC listing,Extended,7931
33 4x0402,RN18,R_Array_Convex_4x0402,C25501,4D02WGJ0330TCE,"Uniroyal 4x0402 array +-5 %, JLC parts library search 2026-11-08 (same family as the 8.2k and 68 ohm arrays)",Extended,268848
68,"RN19,RN20,RN21,RN22",R_Array_Convex_4x0402,C52984,4D02WGJ0680TCE,LCSC listing,Extended,21290
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
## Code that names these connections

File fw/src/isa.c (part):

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}

uint32_t RAM_FUNC(isa_drq)(void) {
    uint32_t h = gpioc_hi_in_get();        // bit0 = GPIO32 = DRQ0
    return (h & 0xFu) | (((h >> 4) & 0x7u) << 5);   // DRQ5..7 are GPIO36..38 -> bits 5..7
}

bool RAM_FUNC(isa_pcirst_n)(void) { return (gpioc_lo_in_get() >> PIN_PCIRST_N) & 1u; }
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// ---------------------------------------------------------------------------------------------
// strobe helpers
// ---------------------------------------------------------------------------------------------
static inline bool rdy(void) { return (gpioc_lo_in_get() >> PIN_IOCHRDY) & 1u; }

static void RAM_FUNC(wait_rdy)(void) {
    if (rdy()) return;
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    gpioc_lo_out_clr(m);
    gpioc_lo_out_set(((uint32_t)(ch & 7) << PIN_DACK_A));
    nops(2);
    gpioc_lo_out_set(M(PIN_AEN));
}
// drop the 138 enable (AEN) before the select lines, or DACK0# glitches
static inline void dack_off(void) {
    gpioc_lo_out_clr(M(PIN_AEN));
    nops(8);
    gpioc_lo_out_clr(M(PIN_DACK_A) | M(PIN_DACK_B) | M(PIN_DACK_C));
}
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}

// 16 bit DMA (channels 5..7): word transfer on SD0..15, SBHE# low, A0 = 0. DACK n# = 138 output n.
#define DMA_WORD (1u << 23)                 // SA = 0, SBHE# = 0; spare bit (U7.QH) so no I/O word equals it: DMA skips the IOCS16# sense
static inline void sbhe_low(void) { if (cur_word != DMA_WORD) chain_addr(DMA_WORD); }   // kept until the next I/O address

uint16_t RAM_FUNC(isa_dma16_read)(unsigned ch, bool tc) {
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    m33_hw->dwt_ctrl |= M33_DWT_CTRL_CYCCNTENA_BITS;
    t_addr = t_idle = cyc();
    // outputs first with their idle level, then direction (the board pulls hold sane levels until here)
    out_pin(PIN_ISA_RUN, false);            // RESETDRV stays asserted, 595 outputs off
    out_pin(PIN_IOR_N, true);
    out_pin(PIN_IOW_N, true);
    out_pin(PIN_SD_OE_N, true);
    out_pin(PIN_SD_DIR, true);
    out_pin(PIN_AEN, false);
    out_pin(PIN_TC, false);
    out_pin(PIN_DACK_A, false);
    out_pin(PIN_DACK_B, false);
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        gpio_set_drive_strength(PIN_IOW_N, GPIO_DRIVE_STRENGTH_8MA);
    }
    // inputs: the board has the pulls
    const uint ins[] = {PIN_CH_MISO, PIN_IOCHRDY, PIN_DRQ0, PIN_DRQ1, PIN_DRQ2, PIN_DRQ3, PIN_DRQ5, PIN_DRQ6, PIN_DRQ7};
    for (unsigned i = 0; i < sizeof ins / sizeof ins[0]; i++) {
        gpio_init(ins[i]);
        gpio_set_dir(ins[i], GPIO_IN);
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
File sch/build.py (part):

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    elif nm == "DVDD": pin += DVDD
    elif nm == "VREG_FB": pin += DVDD
    elif nm in ("ADC_AVDD", "QSPI_IOVDD", "USB_OTP_VDD", "VREG_VIN"): pin += V3
    elif nm == "VREG_AVDD": pin += VREG_AVDD
    elif nm == "VREG_PGND" or nm == "GND": pin += GND
    elif nm == "VREG_LX": pin += VREG_LX
# regulator: L1 3.3 uH between LX and DVDD (dot side = LX), C6 VREG_VIN, C7 4.7u on DVDD, R3 33 + C9 on AVDD
flag(DVDD); flag(VREG_AVDD)
l1 = Part("Device", "L", value="3.3u AOTA-B201610S3R3-101-T", footprint=FP["ind_mcu"]); l1[1] += DVDD; l1[2] += VREG_LX                                            # pad 1 (polarity dot) = +1V1 as on the Raspberry Pi reference board
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R("33", V3, VREG_AVDD); C("4.7u/10V", VREG_AVDD, GND, "c0603")
decouple(DVDD, 3); decouple(V3, 10)                       # 100n per IOVDD/ADC/USB/QSPI/VIN pin pair
C("10u/10V", V3, GND, "c0805"); C("10u/10V", V3, GND, "c0805")
# crystal ABM8-272-T3: XIN pin1, XOUT -> 1k -> pin3, 15 pF each side to GND (reference design)
xt = Part("Device", "Crystal_GND24", value="12MHz ABM8-272-T3", footprint=FP["xtal"])
xin, xo = N("XIN"), N("XOUT"); xo2 = N("XOUT_X")
xt[1] += xin; xt[3] += xo2; xt[2] += GND; xt[4] += GND
mcu["XIN"] += xin; mcu["XOUT"] += xo
R("1k", xo, xo2); C("15p", xin, GND); C("15p", xo2, GND)
# reset / SWD header (Pico debug probe order): pin1 SWCLK, 2 GND, 3 SWDIO, 4 RUN. Flash with picotool/OpenOCD over SWD; no BOOTSEL/UART boot parts.
RUN = N("RUN")
mcu["RUN"] += RUN; R("10k", V3, RUN)
C("100n", RUN, GND)
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
# GPIO wiring from pinmap.py: every MAP name becomes a net named after the signal
sig = {}
DIRECT = {f"DRQ{c}" for c in (0, 1, 2, 3, 5, 6, 7)} | {"IOCHRDY"}      # no buffer: MCU pin = slot net
def S(name):
    """MCU-side net for a pinmap signal. M_ prefix keeps it distinct from the slot-side net of the same name."""
    if name not in sig: sig[name] = N(name) if name in DIRECT else N("M_" + name)
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        for i, (x, y) in enumerate(chunk): pk[i + 1] += x; pk[8 - i] += y
        for i in range(len(chunk), 4): pk[i + 1] += NC; pk[8 - i] += NC

# 33R series damping only where edges are fast or the line is a strobe/clock: SD0-15, IOR#, IOW#, OSC, BCLK, RESETDRV.
# Address, SBHE#, DACK#, AEN, TC change rarely, and dISAppointment (proven with an SB16) has no series resistors on any ISA line.
NO_SERIES = {f"SA{i}" for i in range(20)} | {"SBHE#", "AEN", "TC"} | {f"DACK{c}#" for c in (0, 1, 2, 3, 5, 6, 7)}
def slot_out(name):
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    chip, slot = N(name + "_o"), N(name); (_series68 if name.startswith("SD") else _series).append((chip, slot)); return chip, slot
_series, _series68 = [], []   # SD0-15: 68R (4245A 24 mA edges, simulated: 33R leaves 5.7 V / 22 mA clamp current on long lines); others 33R

RESETDRV = N("RESETDRV")   # internal, active high; 595 OE# and RESETDRV slot pin

# ---- address chain: 3x 74AHCT595 (SA0-15, SBHE#, SA16-19) -------------------------------------------------------
sa_o, sa = zip(*[slot_out(f"SA{i}") for i in range(20)]); sb_o, sb = slot_out("SBHE#")
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st = Part("isa_bridge", "SN74AHCT244", footprint=FP["qfn20"]); vcc_gnd(st, V5_LOG); st[21] += GND
st["1OE"] += GND; st["2OE"] += GND
aen_o, aen = slot_out("AEN")
for pin_in, pin_out, src, name in (("1A0", "1Y0", S("IOR_N"), "IOR#"), ("1A1", "1Y1", S("IOW_N"), "IOW#"), ("1A2", "1Y2", S("AEN"), "AEN"), ("1A3", "1Y3", S("TC"), "TC")):
    if name == "AEN": o = aen_o
    else: o, _ = slot_out(name)
    st[pin_in] += src; st[pin_out] += o
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        o, _ = slot_out(f"SD{k * 8 + i}")
        t[f"A{i + 1}"] += o; t[f"B{i + 1}"] += S(f"SD{k * 8 + i}")

# ---- DRQ + IOCHRDY: slot net and MCU net are the same net, straight to GPIO. GPIO0-39 are 5 V fault tolerant with IOVDD = 3.3 V (RP2350 datasheet 14.8.2.1, 14.9.1).
# ================================================================================================
# 6. Clocks for the slot: 14.31818 MHz oscillator (+3V3_OSC) -> OSC, divided by 2 -> BCLK. RESETDRV.
# ================================================================================================
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    b = Part("74xGxx", "74AHCT1G125", footprint=FP["sot235"]); b[3] += GND; b[5] += V5_LOG; C("100n", V5_LOG, GND)
    b[1] += GND; b[2] += src                              # OE# low = enabled
    o, slotn = slot_out(name); b[4] += o; return slotn
bclk_slot = buf(bq, "BCLK")                                   # no OSC (14.318 MHz) output: dISAppointment leaves ISA pin B30 open, CS4237B has no OSC pin
# RESETDRV = NAND(ISA_RUN, PCIRST#): high (reset) while the host resets or firmware has not released the slot
nd = Part("74xGxx", "74AHCT1G00", footprint=FP["sot235"]); nd[3] += GND; nd[5] += V5_LOG; C("100n", V5_LOG, GND)
nd[1] += S("ISA_RUN"); nd[2] += S("PCIRST_N"); nd[4] += RESETDRV
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R("33", bq_raw, bq)                                                      # source series resistor: 65 mm line, simulated undershoot -0.7 V / 17 mA clamp current at the AHCT input without it, -0.27 V / 0 mA with it

# ---- HG23 additions (appended last so no existing reference moves) ----------------------------------------------------------
for _n in SERIES_MCU: R("33", N("M_" + _n + "_o"), S(_n))                # source termination at the MCU pins: SCK 147 mm, IOR#/IOW# 135 mm, LCLK 160 mm
# DRQ idle-low pull-downs: 4.7k arrays (same part as RN3/RN4)
for _p in list(default_circuit.parts):
    if _p.name == "R_Pack04" and any(getattr(_pin.net, "name", "").startswith("DRQ") for _pin in _p.pins):
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

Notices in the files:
fw/src/isa.c:
SPDX-License-Identifier: GPL-2.0-or-later
